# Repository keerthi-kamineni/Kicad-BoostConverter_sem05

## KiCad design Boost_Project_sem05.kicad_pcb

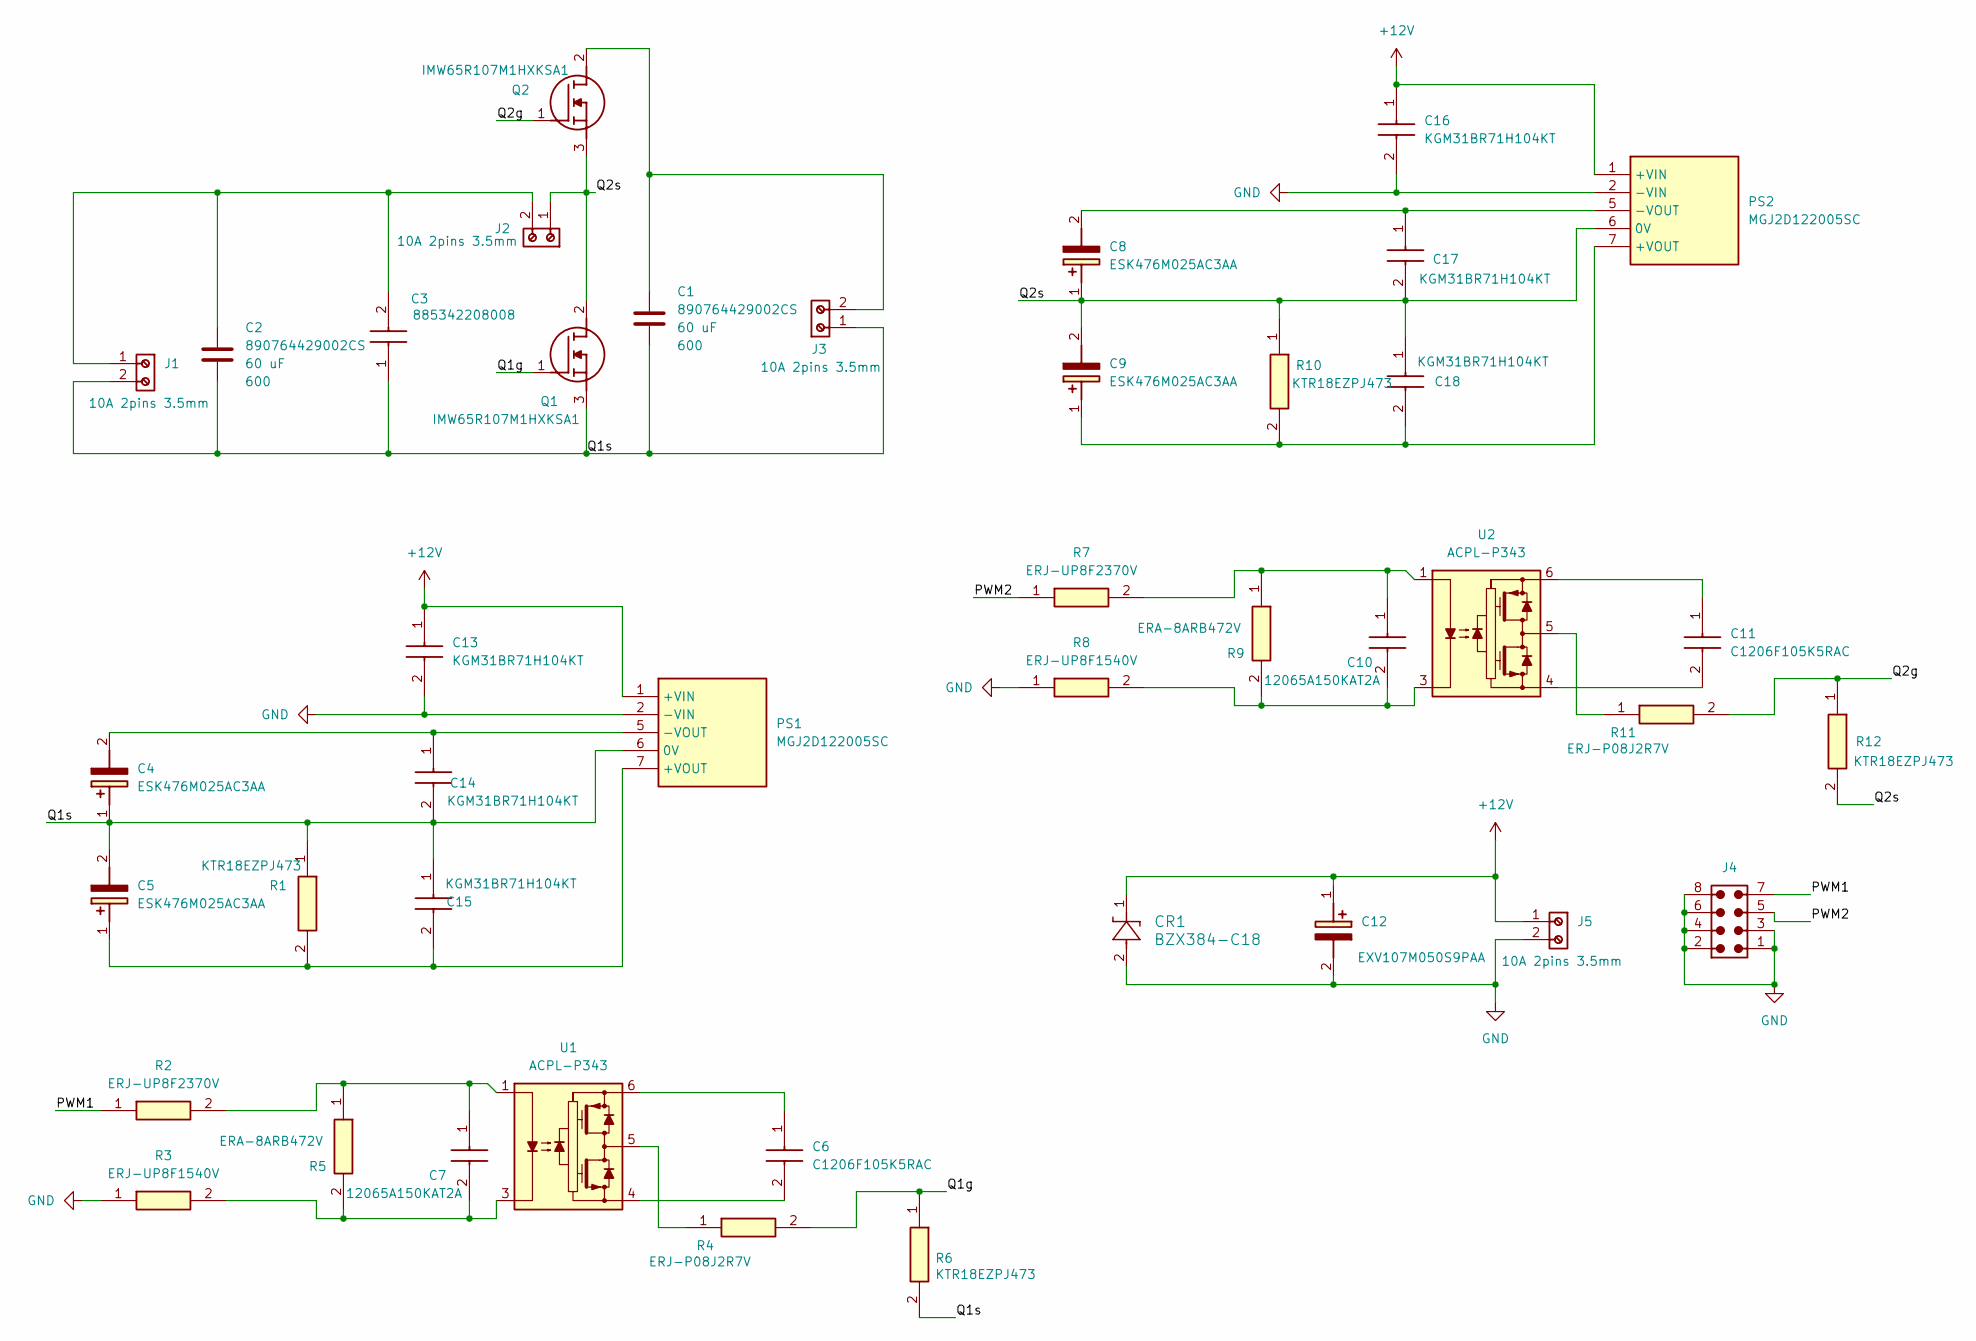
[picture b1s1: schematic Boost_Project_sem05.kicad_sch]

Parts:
C1, C2: 60 uF; 890764429002CS; Voltage 600; Part Number 890764429002CS
C3: 885342208008; CAPC3216X125N; Manufacturer_Part_Number 885342208008
C4, C5, C8, C9: ESK476M025AC3AA; ESW106M016AC3FA; Manufacturer_Part_Number ESK476M025AC3AA
C6, C11: C1206F105K5RAC; CAPC3216X180N; Mouser Part Number 80-C1206F105K5RAC
C7, C10: 12065A150KAT2A; CAPC3216X94N; Mouser Part Number 581-12065A150KAT2A
C12: EXV107M050S9PAA; CAPAE1030X1050N; Manufacturer_Part_Number EXV107M050S9PAA
C13, C14, C15, C16, C17, C18: KGM31BR71H104KT; CAPC3216X94N; Mouser Part Number 581-KGM31BR71H104KT
CR1: BZX384-C18; SC-76_SOD323_NXP
J1, J2, J3, J5: 691214110002; J_Wurth_WR-TBL_691214110002; Part Number 691214110002
J4: 62200821121; J_Wurth_WR-PHD_62200821121
PS1, PS2: MGJ2D122005SC; MGJ2D_7-PIN-SIP; Mouser Part Number 580-MGJ2D122005SC
Q1, Q2: IMW65R107M1HXKSA1; TO544P530X1590X2600-3P; Mouser Part Number 726-IMW65R107M1HXKSA
R1, R6, R10, R12: KTR18EZPJ473; RESC3216X65N; Mouser Part Number 755-KTR18EZPJ473
R2, R7: ERJ-UP8F2370V; ERJUP8; Manufacturer_Part_Number ERJ-UP8F2370V
R3, R8: ERJ-UP8F1540V; ERJUP8; Manufacturer_Part_Number ERJ-UP8F1540V
R4, R11: ERJ-P08J2R7V; ERJP08__1206_; Mouser Part Number 667-ERJ-P08J2R7V
R5, R9: ERA-8ARB472V; RESC3216X70N; Mouser Part Number 667-ERA-8ARB472V
U1, U2: ACPL-P343; SSO-6_6.8x4.6mm_P1.27mm_Clearance7mm

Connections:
+12V: C12.1 (+), C13.1, C16.1, CR1.1, J5.1, PS1.1 (+VIN), PS2.1 (+VIN)
/PWM1: J4.7, R2.1
/PWM2: J4.5, R7.1
/Q1g: Q1.1 (G), R4.2, R6.1
/Q1s: C1.2, C2.2, C3.1, C4.1 (+), C5.2 (-), C14.2, C15.1, J1.2, J3.1, PS1.6 (0V), Q1.3 (S), R1.1, R6.2
/Q2g: Q2.1 (G), R11.2, R12.1
/Q2s: C8.1 (+), C9.2 (-), C17.2, C18.1, J2.1, PS2.6 (0V), Q1.2 (D), Q2.3 (S), R10.1, R12.2
GND: C12.2 (-), C13.2, C16.2, CR1.2, J4.1, J4.2, J4.3, J4.4, J4.6, J4.8, J5.2, PS1.2 (-VIN), PS2.2 (-VIN), R3.1, R8.1
unnamed: C2.1, C3.2, J1.1, J2.2
unnamed: C4.2 (-), C14.1, PS1.5 (-VOUT)
unnamed: C5.1 (+), C15.2, PS1.7 (+VOUT), R1.2
unnamed: C7.1 (C1), R2.2, R5.1, U1.1 (A)
unnamed: C7.2 (C2), R3.2, R5.2, U1.3 (C)
unnamed: C8.2 (-), C17.1, PS2.5 (-VOUT)
unnamed: C9.1 (+), C18.2, PS2.7 (+VOUT), R10.2
unnamed: C10.1 (C1), R7.2, R9.1, U2.1 (A)
unnamed: C10.2 (C2), R8.2, R9.2, U2.3 (C)
unnamed: C1.1, J3.2, Q2.2 (D)
unnamed: C6.1, U1.6 (VCC)
unnamed: C6.2, U1.4 (VEE)
unnamed: R4.1, U1.5 (VO)
unnamed: C11.1, U2.6 (VCC)
unnamed: C11.2, U2.4 (VEE)
unnamed: R11.1, U2.5 (VO)

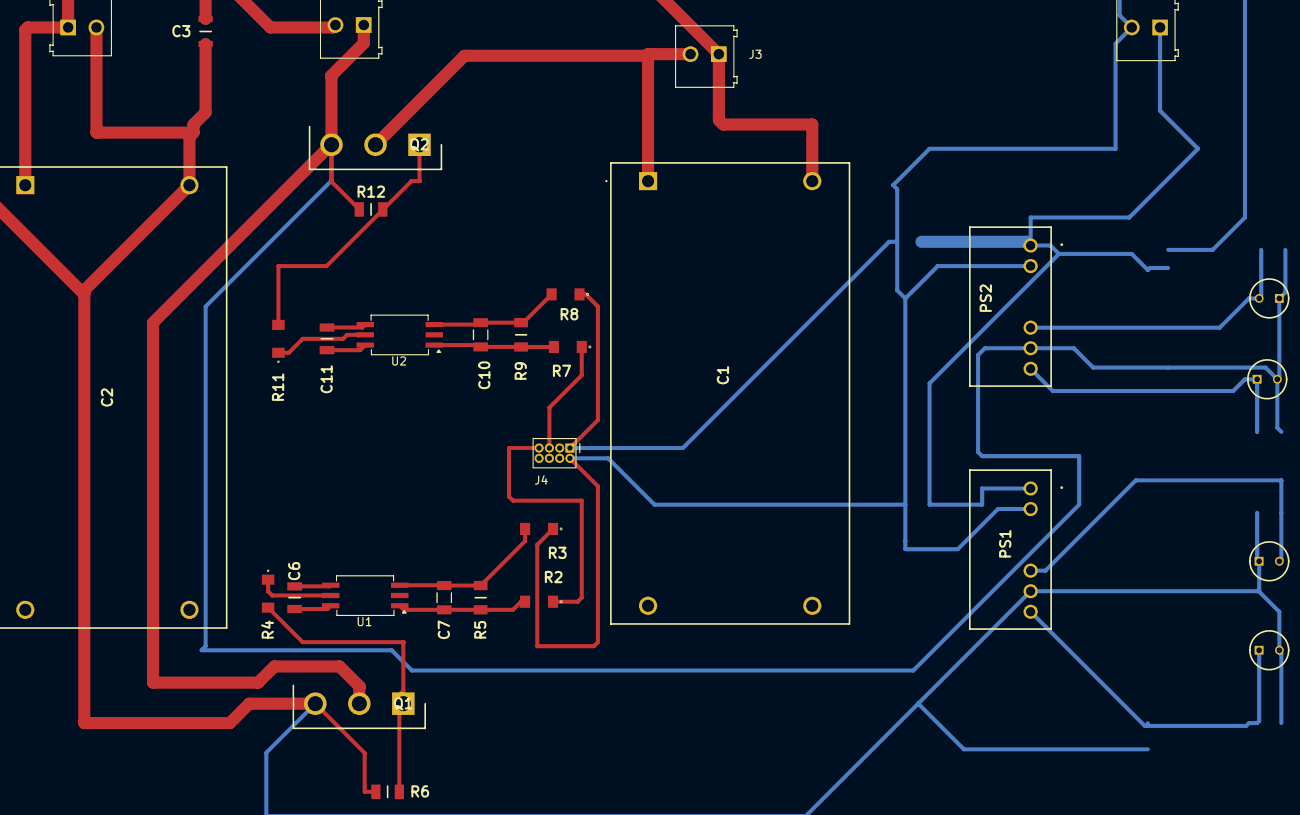
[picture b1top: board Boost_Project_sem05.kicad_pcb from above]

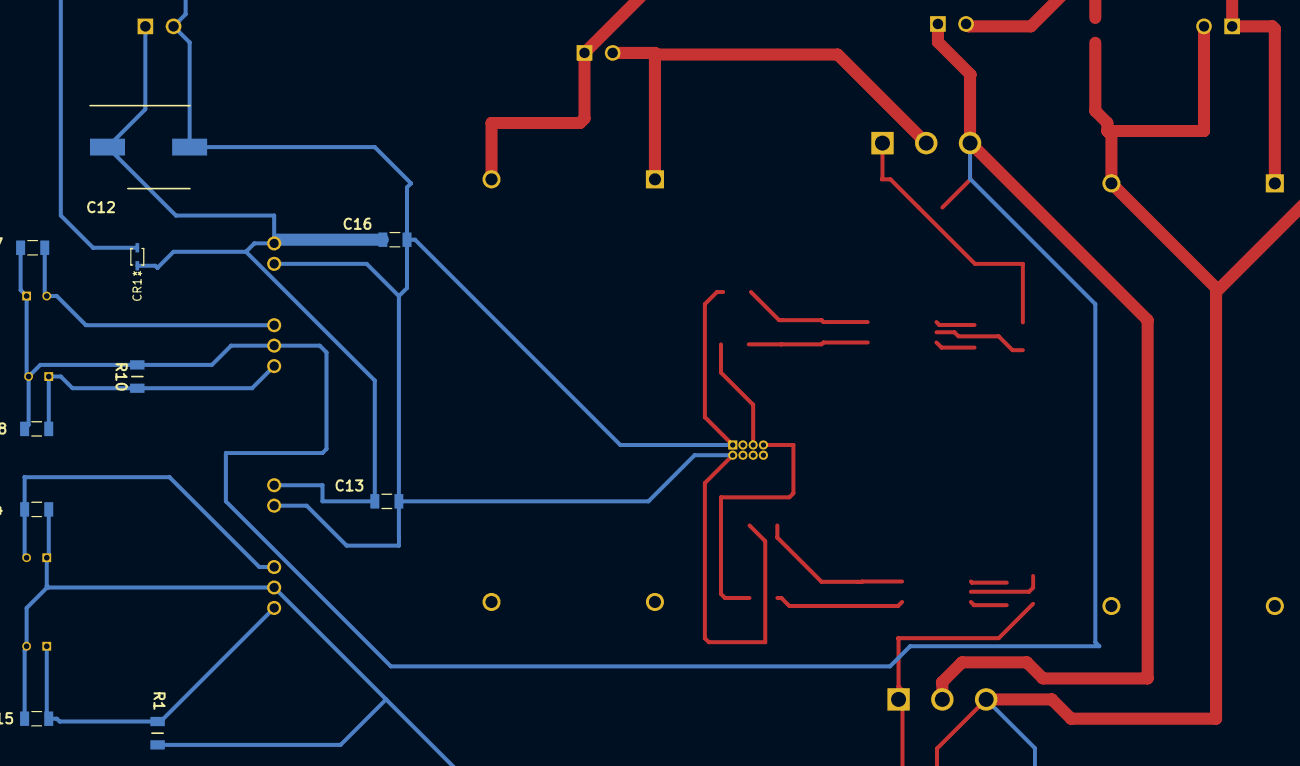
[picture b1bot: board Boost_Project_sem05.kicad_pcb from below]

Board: 2 copper layers, 42 parts (10 on the bottom side), 24 nets.
